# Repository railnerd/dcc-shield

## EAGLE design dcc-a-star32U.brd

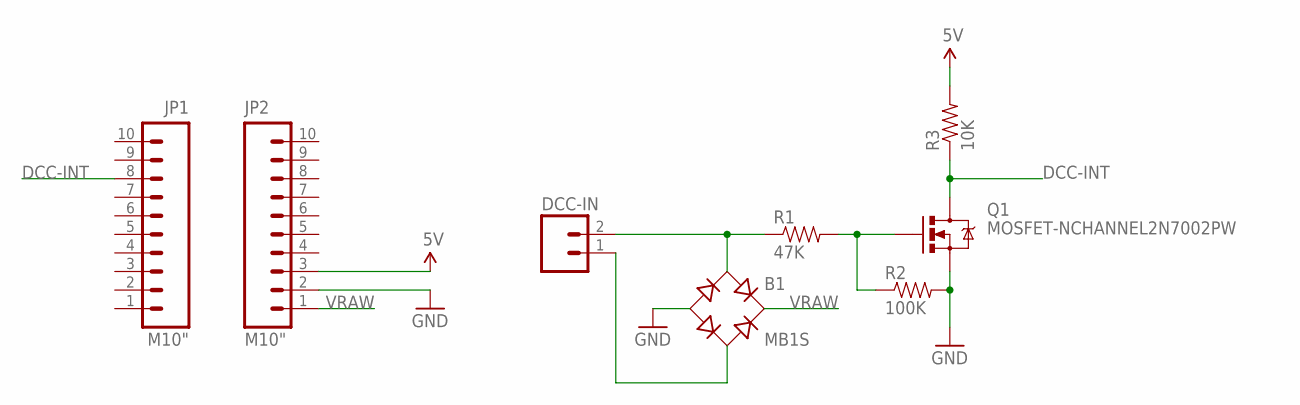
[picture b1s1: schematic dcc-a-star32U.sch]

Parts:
B1: MB1S; SOIC-4
DCC-IN: M02-JST-2-PTH-NO_SILK; JST-2-PTH-NS
JP1, JP2: M10"; 1X10
Q1: MOSFET-NCHANNEL2N7002PW; SOT323
R1: 47K; 0603-RES
R2: 100K; 0603-RES
R3: 10K; 0603-RES

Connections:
5V: JP2.3, R3.2
DCC-INT: JP1.8, Q1.3 (D), R3.1
GND: B1.-, JP2.2, Q1.2 (S), R2.2
unnamed: Q1.1 (G), R1.2, R2.1
unnamed: B1.~1 (AC1), DCC-IN.2, R1.1
unnamed: B1.~2 (AC2), DCC-IN.1
VRAW: B1.+, JP2.1

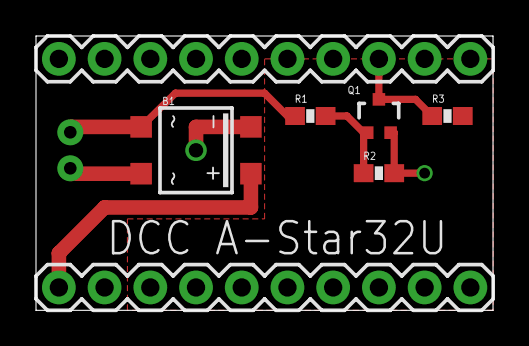
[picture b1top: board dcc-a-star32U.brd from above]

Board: 4 copper layers, 25.4 x 15.2 mm, 8 parts (0 on the bottom side), 7 nets.

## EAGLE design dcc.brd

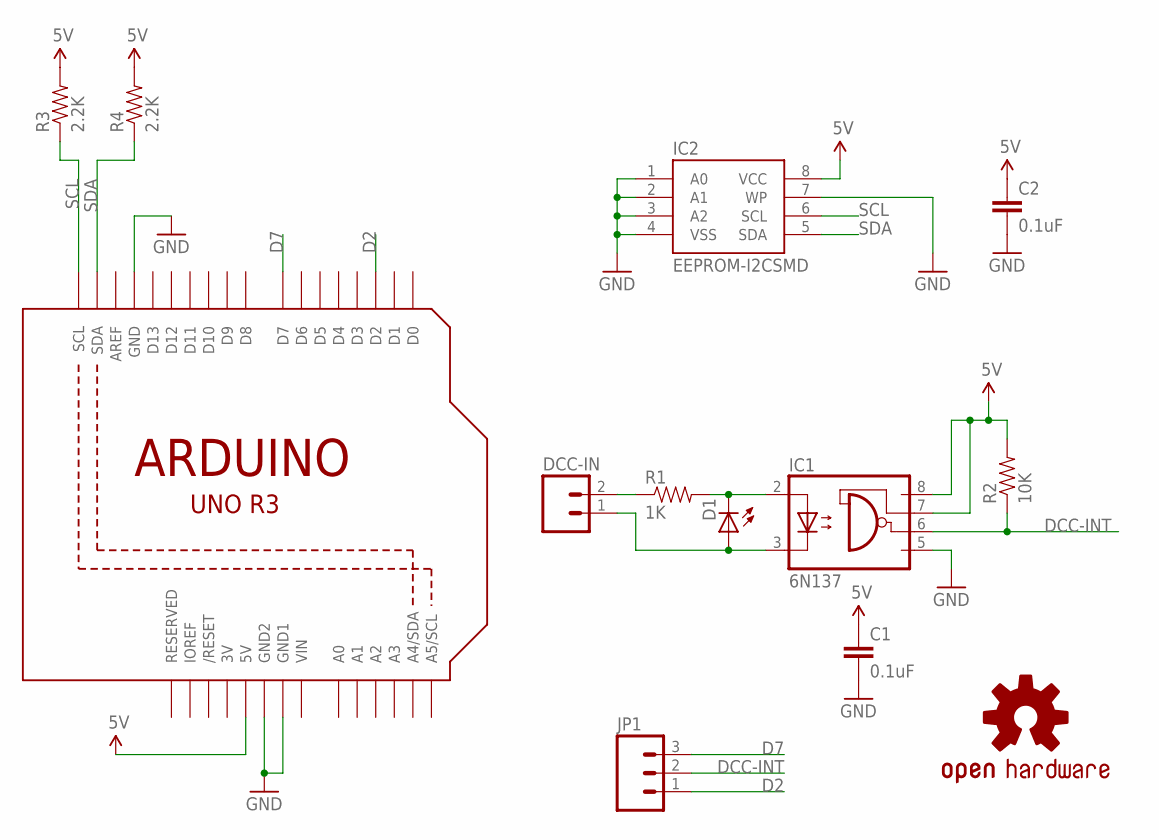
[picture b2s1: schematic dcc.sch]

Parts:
C1: 0.1uF; CAP-PTH-SMALL
C2: 0.1uF; 0603-CAP
D1: LED5MM
DCC-IN: M025MM; SCREWTERMINAL-5MM-2
IC1: 6N137; DIL08
IC2: EEPROM-I2CSMD; SO08
JP1: M03PTH; 1X03
LOGO1: OSHW-LOGOL; OSHW-LOGO-L
R1: 1K; AXIAL-0.4
R2: 10K; AXIAL-0.4
R3, R4: 2.2K; 0603-RES
U1: ARDUINOR3-JUSTPINS; ARDUINOR3

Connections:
3V: U1.3V
5V: C1.1, C2.1, IC1.7 (VE), IC1.8 (VCC), IC2.8 (VCC), R2.P$2 (2), R3.2, R4.2, U1.5V
D1: D1.K (C), IC1.2 (A), R1.P$2 (2)
D2: JP1.1, U1.D2
D7: JP1.3, U1.D7
DCC-INT: IC1.6 (VO), JP1.2, R2.P$1 (1)
GND: C1.2, C2.2, IC1.5 (GND), IC2.1 (A0), IC2.2 (A1), IC2.3 (A2), IC2.4 (VSS), IC2.7 (WP), U1.GND, U1.GND1, U1.GND2
unnamed: DCC-IN.2, R1.P$1 (1)
unnamed: D1.A, DCC-IN.1, IC1.3 (C)
SCL: IC2.6 (SCL), R3.1, U1.SCL
SDA: IC2.5 (SDA), R4.1, U1.SDA
VIN: U1.VIN

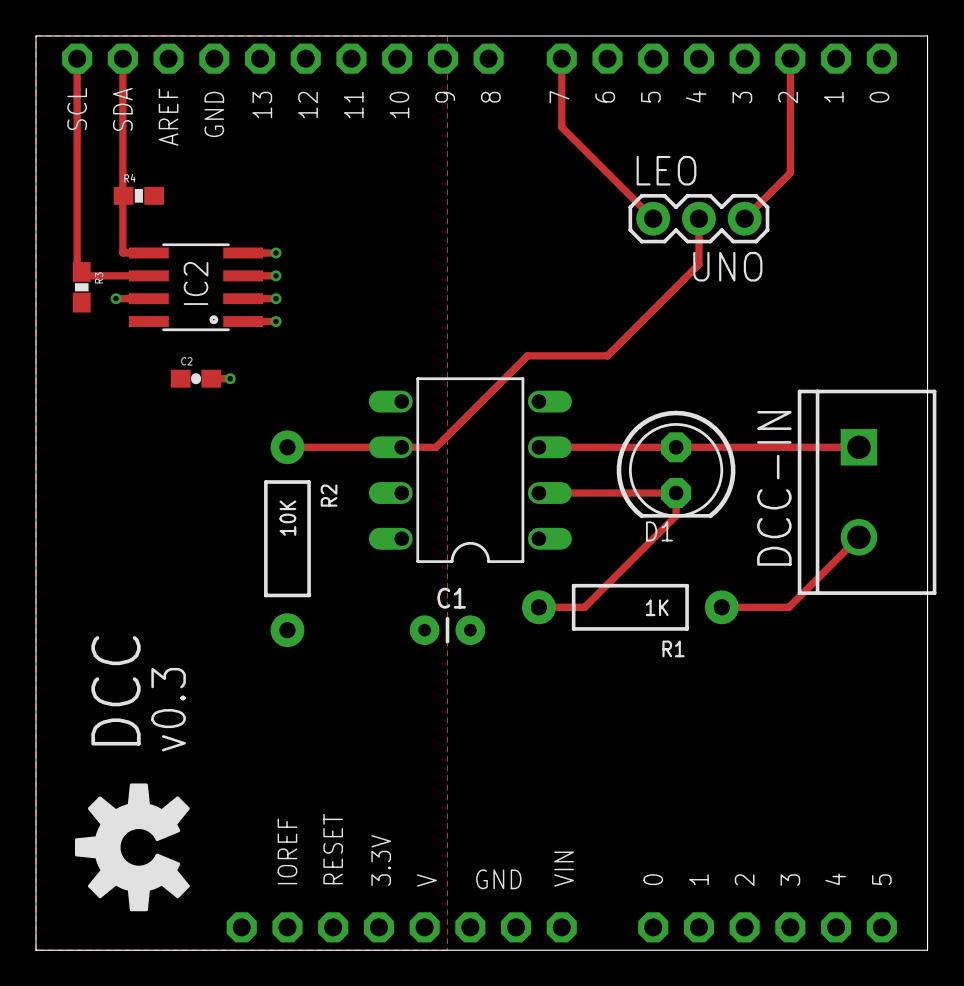
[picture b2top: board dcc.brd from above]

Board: 4 copper layers, 49.5 x 50.8 mm, 13 parts (0 on the bottom side), 10 nets.

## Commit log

2014-06-27 add pro-mini and pro-micro boards
    Added DCC-powered decoder boards for the SparkFun Arduino Pro Micro and
    Pro Mini form factors.
2014-07-28 add a-star variant, use JST for dcc-powered boards
2015-01-31 tweaked isolation
2015-04-12 fabbed version
    increase padding, minor tweaks

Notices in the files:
parts and their libraries:
SparkFun-Connectors: Licensing: CC v3.0 Share-Alike You are welcome to use this library for commercial purposes.
SparkFun-Passives: Licensing: Creative Commons ShareAlike 4.0 International - https://creativecommons.org/licenses/by-sa/4.0
